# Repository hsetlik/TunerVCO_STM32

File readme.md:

# Eurorack VCO with STM32-powered tuner

This repo contains the code, schematic, and PCB design for a full-featured voltage controlled oscillator with an OLED-based tuner in a 9HP Eurorack module. The VCO is
built around the [AS3340 IC from Alfa](https://www.alfarzpp.lv/eng/sc/AS3340.pdf), while the tuner is powered by an [STM32G030F6P6 microcontroller](https://www.st.com/en/microcontrollers-microprocessors/stm32g030f6.html).

## Background

This is an improved version of my earlier [tuner VCO module](https://github.com/hsetlik/TunerVCO). The old one runs on an ESP32 WROOM cannibalized from an unused dev board I had lying around, with firmware written in the Arduino framework.
The old ESP32 version works fine and sounds great, but I decided it was worthwhile to make an updated version based on a different MCU for a few reasons:

1. The ESP32 is far larger and more powerful than this little OLED tuner needs
2. The ESP32 WROOM module and its associated components (USB connector, USB-to-UART bridge, BJTs, etc.) take up a lot of space on the PCB, which necessitated a horrible design involving right-angle header pins on the first version.
3. I also put the pots too close together on the first version and the knobs didn't fit

## Hardware

I've included the full KiCad project inside the 'Schematic' directory. The PCB is 4 layers with the two internal layers as ground planes. Passives and semiconductors are in SMD packages except for the AS3340 which is in a DIP-16 package.

### 3340-based VCO

The analog part of the circuit is mostly derived from the [AS3340 datasheet](https://www.alfarzpp.lv/eng/sc/AS3340.pdf) and so isn't super interesting, but a couple things worth mentioning:

1. The two trim pots to adjust the 1V/oct tracking are mounted such that they can be adjusted from the front panel without taking the module out of the case
2. There's an output stage based on summing op-amps to both isolate the AS3340 from the output jacks and to bias all three waves to a +/- 5V range

### STM32-based tuner

Out of the whole STM32 lineup I settled on the STM32G030F6P6 because

1. The TSSOP-20 package is the perfect size for the module's form factor
2. It requires no external components
3. Relatively low cost

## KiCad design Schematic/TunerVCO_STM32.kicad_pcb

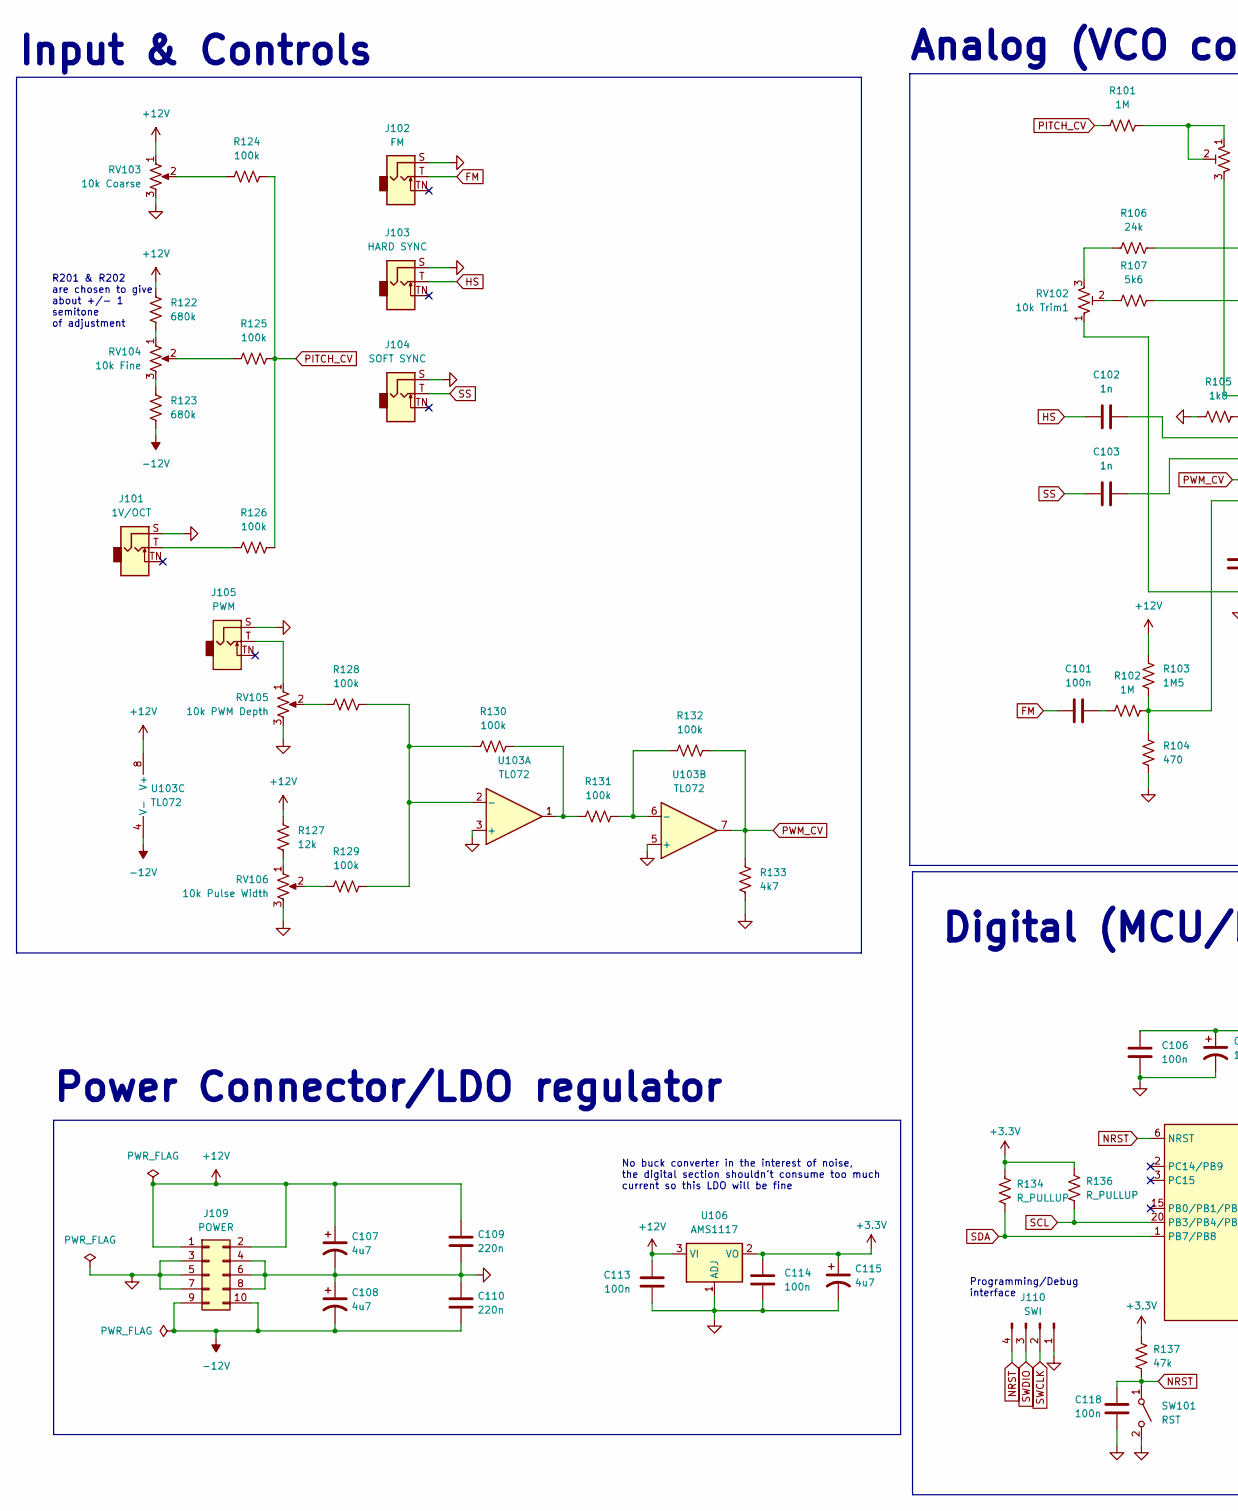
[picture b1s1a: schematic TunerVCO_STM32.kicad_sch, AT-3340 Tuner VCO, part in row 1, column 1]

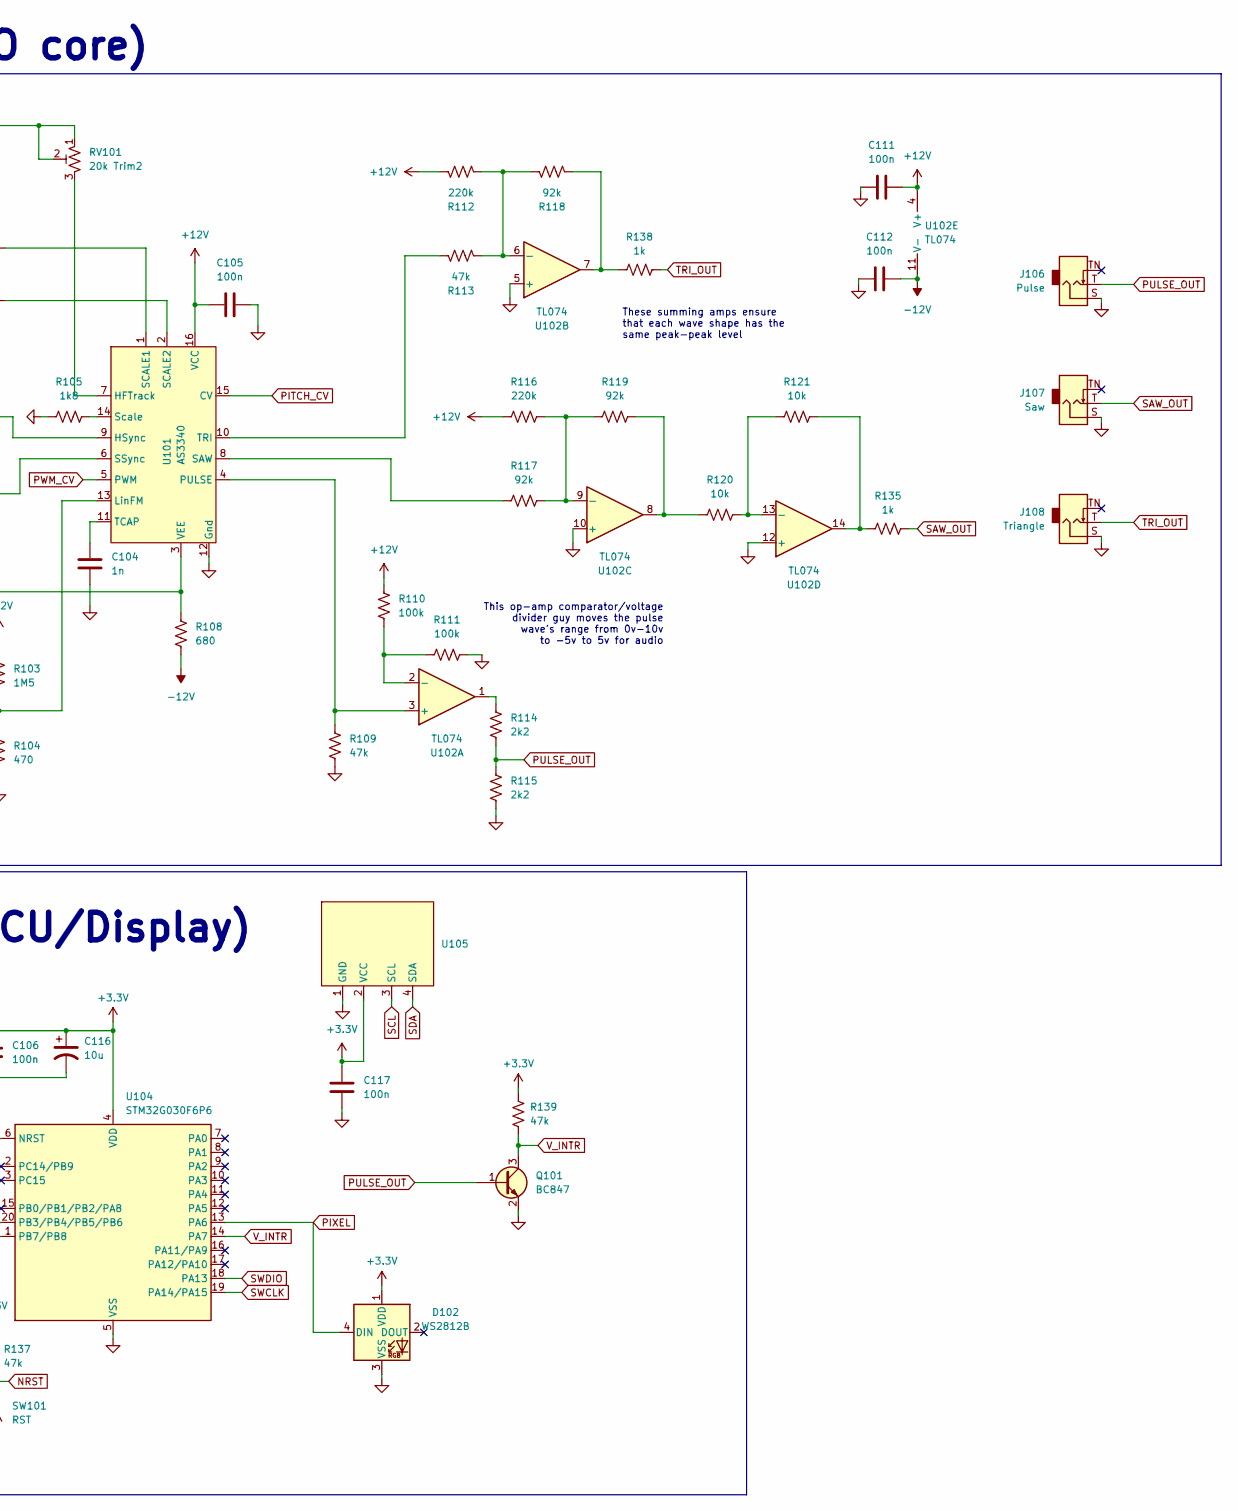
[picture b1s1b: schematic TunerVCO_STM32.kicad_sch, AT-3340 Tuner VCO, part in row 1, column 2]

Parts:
C101, C105, C106, C111, C112, C113, C114, C117, C118: 100n; C_0805_2012Metric
C102, C103, C104: 1n; C_0805_2012Metric
C107, C108, C115: 4u7; CP_Radial_D5.0mm_P2.50mm
C109, C110: 220n; C_0805_2012Metric
C116: 10u; CP_Radial_D5.0mm_P2.50mm
D102: WS2812B; LED_WS2812B_PLCC4_5.0x5.0mm_P3.2mm
J101: 1V/OCT; Jack_3.5mm_QingPu_WQP-PJ398SM_Vertical_CircularHoles
J102: FM; Jack_3.5mm_QingPu_WQP-PJ398SM_Vertical_CircularHoles
J103: HARD SYNC; Jack_3.5mm_QingPu_WQP-PJ398SM_Vertical_CircularHoles
J104: SOFT SYNC; Jack_3.5mm_QingPu_WQP-PJ398SM_Vertical_CircularHoles
J105: PWM; Jack_3.5mm_QingPu_WQP-PJ398SM_Vertical_CircularHoles
J106: Pulse; Jack_3.5mm_QingPu_WQP-PJ398SM_Vertical_CircularHoles
J107: Saw; Jack_3.5mm_QingPu_WQP-PJ398SM_Vertical_CircularHoles
J108: Triangle; Jack_3.5mm_QingPu_WQP-PJ398SM_Vertical_CircularHoles
J109: POWER; PinHeader_2x05_P2.54mm_Vertical
J110: SWI; PinHeader_1x04_P2.54mm_Vertical
Q101: BC847; SOT-23
R101, R102: 1M; R_0805_2012Metric
R103: 1M5; R_0805_2012Metric
R104: 470; R_0805_2012Metric
R105: 1k8; R_0805_2012Metric
R106: 24k; R_0805_2012Metric
R107: 5k6; R_0805_2012Metric
R108: 680; R_0805_2012Metric
R109, R113, R137, R139: 47k; R_0805_2012Metric
R110, R111, R124, R125, R126, R128, R129, R130, R131, R132: 100k; R_0805_2012Metric
R112, R116: 220k; R_0805_2012Metric
R114, R115: 2k2; R_0805_2012Metric
R117, R118, R119: 92k; R_0805_2012Metric
R120, R121: 10k; R_0805_2012Metric
R122, R123: 680k; R_0805_2012Metric
R127: 12k; R_0805_2012Metric
R133: 4k7; R_0805_2012Metric
R134, R136: R_PULLUP; R_0805_2012Metric
R135, R138: 1k; R_0805_2012Metric
RV101: 20k Trim2; Potentiometer_Bourns_3266Y_Vertical
RV102: 10k Trim1; Potentiometer_Bourns_3266Y_Vertical
RV103: 10k Coarse; Potentiometer_Alps_RK09L_Single_Vertical
RV104: 10k Fine; Potentiometer_Alps_RK09L_Single_Vertical
RV105: 10k PWM Depth; Potentiometer_Alps_RK09L_Single_Vertical
RV106: 10k Pulse Width; Potentiometer_Alps_RK09L_Single_Vertical
SW101: RST; SW_SPST_B3U-1000P
U101: AS3340; DIP-16_W7.62mm
U102: TL074; SOIC-14_3.9x8.7mm_P1.27mm
U103: TL072; SOIC-8_3.9x4.9mm_P1.27mm
U104: STM32G030F6P6; TSSOP-20_4.4x6.5mm_P0.65mm
U105: SSD1306_OLED_128x64
U106: AMS1117; SOT-223-3_TabPin2

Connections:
+3.3V: C106.2, C114.2, C115.1, C116.1, C117.2, D102.1 (VDD), R134.2, R136.2, R137.1, R139.1, U104.4 (VDD), U105.2 (VCC), U106.2 (VO)
+12V: C105.1, C107.1, C109.2, C111.2, C113.2, J109.1, J109.2, R103.2, R110.1, R112.1, R116.1, R122.1, R127.2, RV103.1, U101.16 (VCC), U102.4 (V+), U103.8 (V+), U106.3 (VI)
-12V: C108.2, C110.1, C112.2, J109.9, J109.10, R108.1, R123.2, U102.11 (V-), U103.4 (V-)
FM: C101.1, J102.T
GND: C104.1, C105.2, C106.1, C107.2, C108.1, C109.1, C110.2, C111.1, C112.1, C113.1, C114.1, C115.2, C116.2, C117.1, C118.1, D102.3 (VSS), J101.S, J102.S, J103.S, J104.S, J105.S, J106.S, J107.S, J108.S, J109.3, J109.4, J109.5, J109.6, J109.7, J109.8, J110.1, Q101.2 (E), R104.1, R105.1, R109.2, R111.2, R115.2, R133.1, RV103.3, RV105.3, RV106.3, SW101.2 (B), U101.12 (Gnd), U102.5 (+), U102.10 (+), U102.12 (+), U103.3 (+), U103.5 (+), U104.5 (VSS), U105.1 (GND), U106.1 (ADJ)
HS: C102.1, J103.T
NRST: C118.2, J110.4, R137.2, SW101.1 (A), U104.6 (NRST)
unnamed: C101.2, R102.2
unnamed: J101.T, R126.1
unnamed: J105.T, RV105.1
unnamed: R101.2, RV101.1, RV101.2
unnamed: R106.1, RV102.3
unnamed: R107.1, RV102.2
unnamed: R114.1, U102.1
unnamed: R118.2, R138.1, U102.7
unnamed: R119.2, R120.1, U102.8
unnamed: R121.2, R135.1, U102.14
unnamed: R122.2, RV104.1
unnamed: R123.1, RV104.3
unnamed: R124.1, RV103.2
unnamed: R125.1, RV104.2
unnamed: R127.1, RV106.1
unnamed: R128.1, RV105.2
unnamed: R129.1, RV106.2
unnamed: R130.2, R131.1, U103.1
unnamed: RV101.3, U101.7 (HFTrack)
unnamed: C102.2, U101.9 (HSync)
unnamed: R102.1, R103.1, R104.2, U101.13 (LinFM)
unnamed: R109.1, U101.4 (PULSE), U102.3 (+)
unnamed: R117.1, U101.8 (SAW)
unnamed: R106.2, U101.1 (SCALE1)
unnamed: R107.2, U101.2 (SCALE2)
unnamed: C103.2, U101.6 (SSync)
unnamed: R105.2, U101.14 (Scale)
unnamed: C104.2, U101.11 (TCAP)
unnamed: R113.1, U101.10 (TRI)
unnamed: R108.2, RV102.1, U101.3 (VEE)
unnamed: R110.2, R111.1, U102.2 (-)
unnamed: R112.2, R113.2, R118.1, U102.6 (-)
unnamed: R116.2, R117.2, R119.1, U102.9 (-)
unnamed: R120.2, R121.1, U102.13 (-)
unnamed: R128.2, R129.2, R130.1, U103.2 (-)
unnamed: R131.2, R132.1, U103.6 (-)
PITCH_CV: R101.1, R124.2, R125.2, R126.2, U101.15 (CV)
PIXEL: D102.4 (DIN), U104.13 (PA6)
PULSE_OUT: J106.T, Q101.1 (B), R114.2, R115.1
PWM_CV: R132.2, R133.2, U101.5 (PWM), U103.7
SAW_OUT: J107.T, R135.2
SCL: R136.1, U104.20 (PB3/PB4/PB5/PB6), U105.3 (SCL)
SDA: R134.1, U104.1 (PB7/PB8), U105.4 (SDA)
SS: C103.1, J104.T
SWCLK: J110.2, U104.19 (PA14/PA15)
SWDIO: J110.3, U104.18 (PA13)
TRI_OUT: J108.T, R138.2
V_INTR: Q101.3 (C), R139.2, U104.14 (PA7)

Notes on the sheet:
Analog (VCO core)
Power Connector/LDO regulator
Programming/Debug interface
These summing amps ensure that each wave shape has the same peak-peak level
R201 & R202 are chosen to give about +/- 1 semitone of adjustment
Input & Controls
Digital (MCU/Display)
This op-amp comparator/voltage divider guy moves the pulse wave's range from 0v-10v to -5v to 5v for audio
No buck converter in the interest of noise, the digital section shouldn't consume too much current so this LDO will be fine

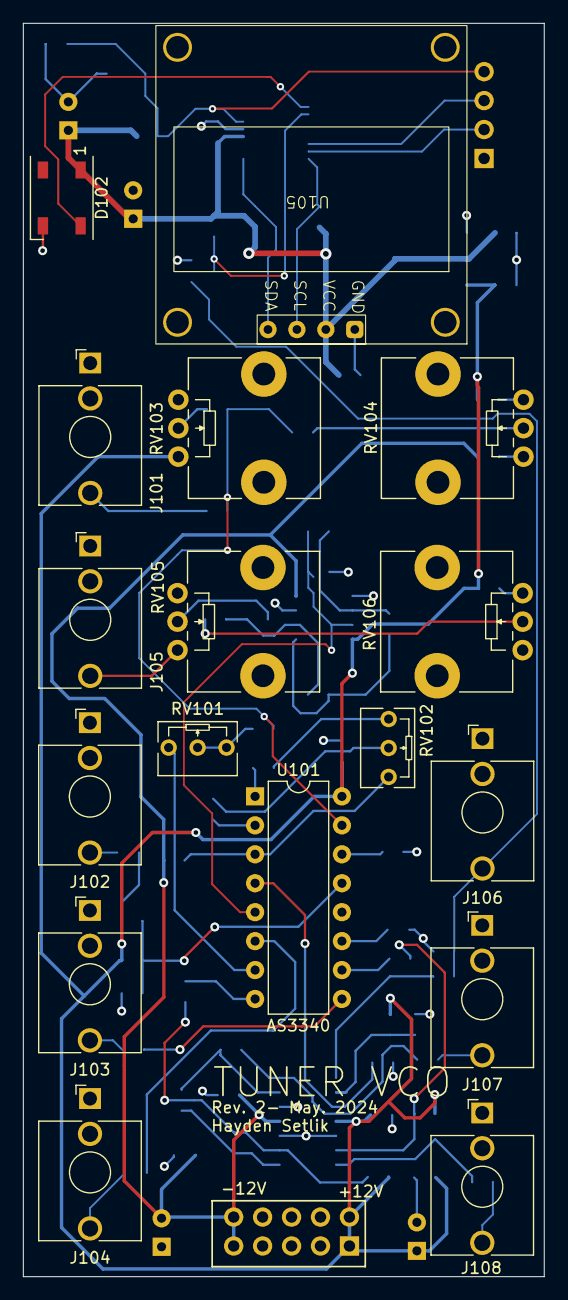
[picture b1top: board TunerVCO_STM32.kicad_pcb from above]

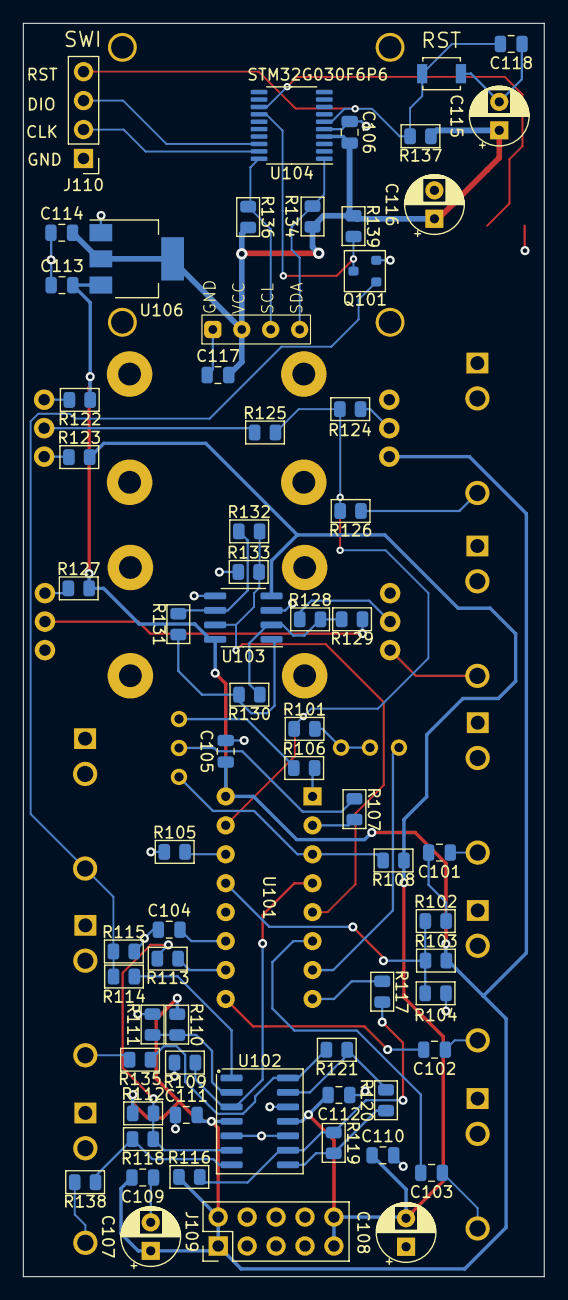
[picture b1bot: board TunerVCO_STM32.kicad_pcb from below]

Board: 4 copper layers, 45.7 x 110.0 mm, 82 parts (65 on the bottom side), 55 nets.

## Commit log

2024-05-06 added schematic and board to git
2024-05-06 display update code
2024-05-06 added readme
2024-05-08 Interrupt config, ISRs in main.c
2024-05-08 NeoPixel Timer/DMA stuff
2024-05-08 pulse width LED
2024-05-08 main while loop, fixed pinout
